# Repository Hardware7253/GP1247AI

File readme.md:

# GP1247AI Driver Board
A GP1247AI clock and animation player, the PCB can also be used as a standalone power supply for the display with external SPI communication through a 10-pin IDC connector.

The [Code](/Code) directory contains the C code for the microcontroller and Python cli tools for syncing the RTC, and writing animations to the device over USB CDC.

## Pictures

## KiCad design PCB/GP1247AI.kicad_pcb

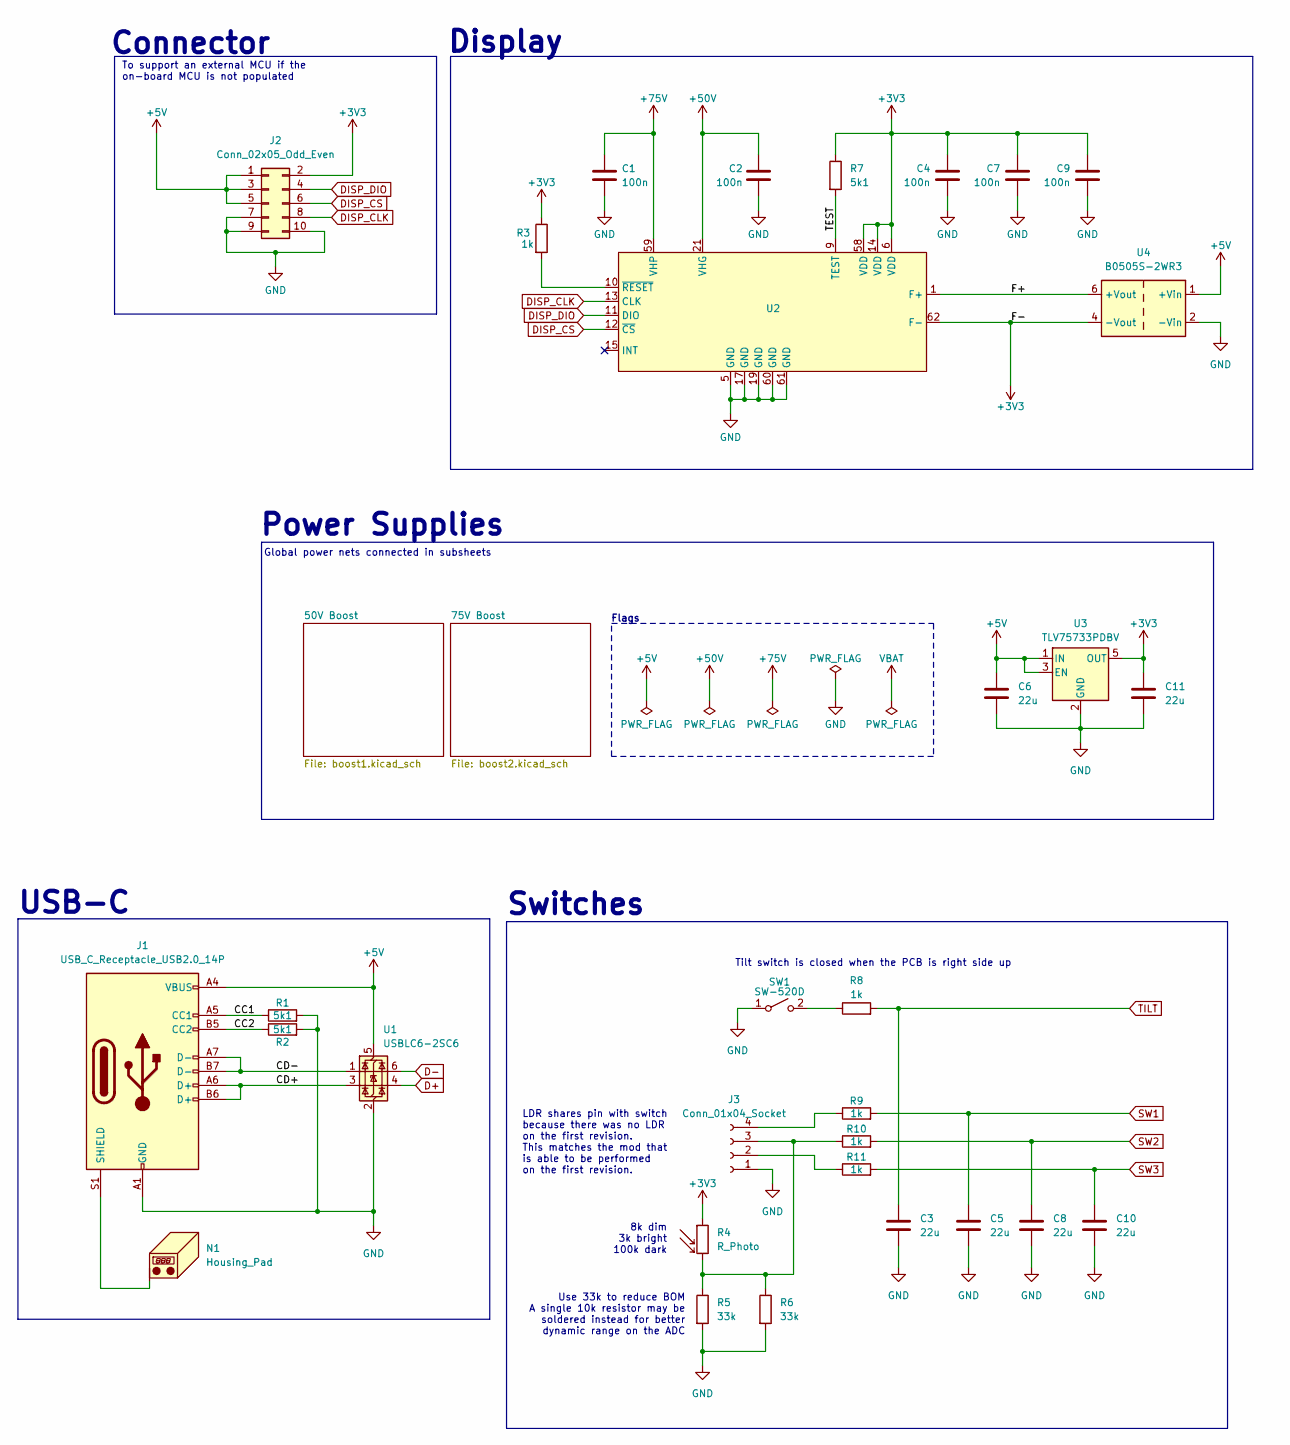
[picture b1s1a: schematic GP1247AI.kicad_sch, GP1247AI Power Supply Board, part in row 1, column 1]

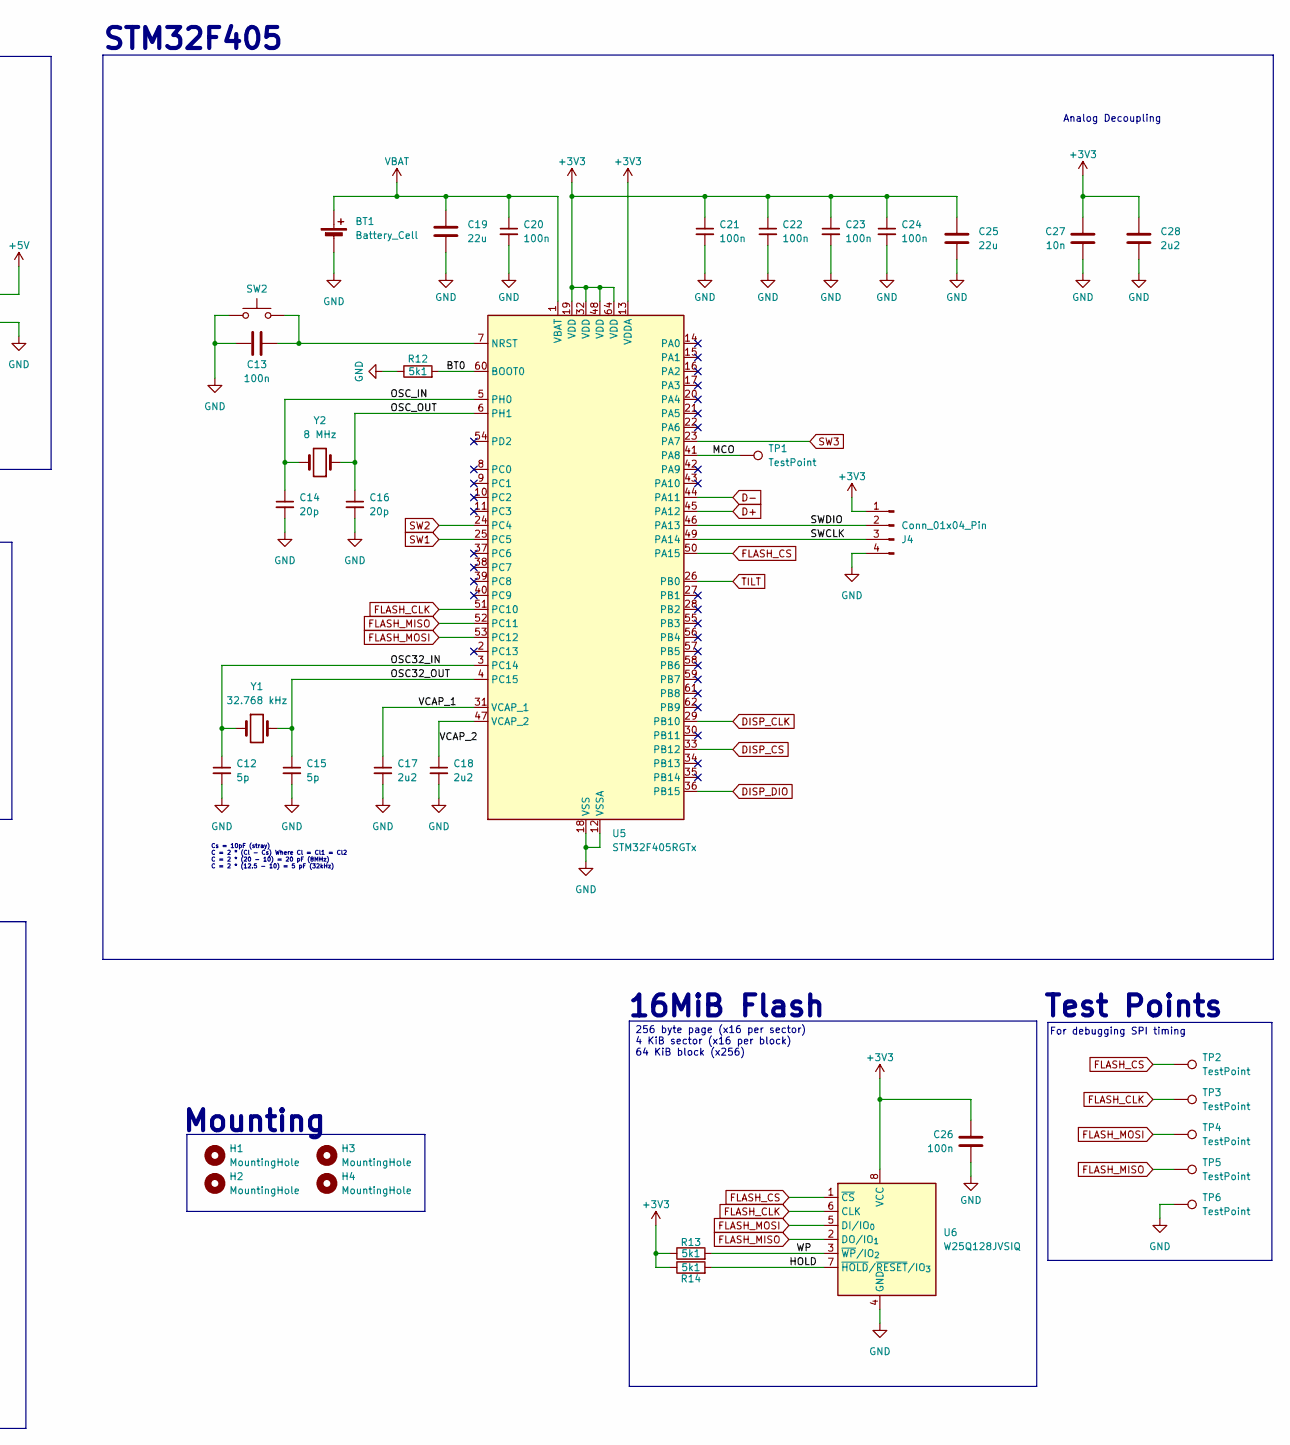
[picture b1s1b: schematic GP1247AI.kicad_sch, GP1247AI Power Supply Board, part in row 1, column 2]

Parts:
BT1: Battery_Cell; QIJEY CR2032-BS-6-1; LCSC PART # C70377
C1, C2, C4, C7, C9, C13, C20, C21, C22, C23, C24, C26: 100n; C_0603_1608Metric; LCSC PART # C15725
C3, C5, C6, C8, C10, C11, C19, C25: 22u; C_0603_1608Metric; LCSC PART # C7432770
C12, C15: 5p; C_0603_1608Metric; LCSC PART # C327203
C14, C16: 20p; C_0603_1608Metric; LCSC PART # C326779
C17, C18, C28: 2u2; C_0603_1608Metric; LCSC PART # C23630
C27: 10n; C_0603_1608Metric; LCSC PART # C15725
H1, H2, H3, H4: MountingHole; MountingHole_3.2mm_M3
J1: USB_C_Receptacle_USB2.0_14P; USB_TYPE-C-31-M-12; LCSC PART # C165948
J2: Conn_02x05_Odd_Even; IDC-Header_2x05_P2.54mm_Vertical
J3: Conn_01x04_Socket; PinSocket_1x04_P2.54mm_Horizontal; LCSC PART # C2897386
J4: Conn_01x04_Pin; PinHeader_1x04_P2.54mm_Vertical
N1: Housing_Pad; TestPoint_Pad_2.0x2.0mm
R1, R2, R7, R12, R13, R14: 5k1; R_0603_1608Metric; LCSC PART # C23186
R3, R8, R9, R10, R11: 1k; R_0603_1608Metric; LCSC PART # C2907002
R4: R_Photo; R_LDR_5.1x4.3mm_P3.4mm_Vertical; LCSC PART # C125626
R5, R6: 33k; R_0603_1608Metric; LCSC PART # C2907028
SW1: SW-520D; LCSC PART # C2905288
SW2: SW_Push; Korean Hroparts Elec K2-1107ST-A4DW-06; LCSC PART # C118141
TP1: TestPoint; TestPoint_Pad_D1.5mm
TP2, TP3, TP4, TP5, TP6: TestPoint; TestPoint_Keystone_5019_Miniature; LCSC PART # C5199800
U1: USBLC6-2SC6; SOT-23-6; LCSC PART # C7519
U2: GP1247AI
U3: TLV75733PDBV; SOT-23-5; LCSC PART # C485517
U4: B0505S-2WR3; LCSC PART # C7465195
U5: STM32F405RGTx; LQFP-64_10x10mm_P0.5mm; LCSC PART # C15742
U6: W25Q128JVSIQ; SOIC-8_5.3x5.3mm_P1.27mm; LCSC PART # C2613930
Y1: 32.768 kHz; SMD3215-2P; LCSC PART # C42438016
Y2: 8 MHz; Crystal_SMD_5032-2Pin_5.0x3.2mm; LCSC PART # C46613796

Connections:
+3V3: C4.1, C7.1, C9.1, C11.1, C21.1, C22.1, C23.1, C24.1, C25.1, C26.1, C27.1, C28.1, J2.2, J4.1, R3.1, R4.1, R7.1, R13.1, R14.1, U2.6 (VDD), U2.14 (VDD), U2.58 (VDD), U2.62 (F-), U2.63 (F-), U2.64 (F-), U2.65 (F-), U3.5 (OUT), U4.4 (-Vout), U5.13 (VDDA), U5.19 (VDD), U5.32 (VDD), U5.48 (VDD), U5.64 (VDD), U6.8 (VCC)
+5V: C6.1, J1.A4 (VBUS), J1.A9 (VBUS), J1.B4 (VBUS), J1.B9 (VBUS), J2.1, J2.3, J2.5, U1.5 (VBUS), U3.1 (IN), U3.3 (EN), U4.1 (+Vin); also elsewhere on the board
+50V: C2.1, U2.21 (VHG); also elsewhere on the board
+75V: C1.1, U2.59 (VHP); also elsewhere on the board
/BT0: R12.2, U5.60 (BOOT0)
/CC1: J1.A5 (CC1), R1.1
/CC2: J1.B5 (CC2), R2.1
/CD+: J1.A6 (D+), J1.B6 (D+), U1.3 (I/O2)
/CD-: J1.A7 (D-), J1.B7 (D-), U1.1 (I/O1)
/F+: U2.1 (F+), U2.2 (F+), U2.3 (F+), U2.4 (F+), U4.6 (+Vout)
/HOLD: R14.2, U6.7 (~HOLD/~RESET/IO_{3})
/MCO: TP1.1 (1_1), U5.41 (PA8)
/OSC32_IN: C12.1, U5.3 (PC14), Y1.1
/OSC32_OUT: C15.1, U5.4 (PC15), Y1.2
/OSC_IN: C14.1, U5.5 (PH0), Y2.2
/OSC_OUT: C16.1, U5.6 (PH1), Y2.1
/SWCLK: J4.3, U5.49 (PA14)
/SWDIO: J4.2, U5.46 (PA13)
/TEST: R7.2, U2.9 (TEST)
/VCAP_1: C17.1, U5.31 (VCAP_1)
/VCAP_2: C18.1, U5.47 (VCAP_2)
/WP: R13.2, U6.3 (~WP/IO_{2})
D+: U1.4 (I/O2), U5.45 (PA12)
D-: U1.6 (I/O1), U5.44 (PA11)
DISP_CLK: J2.8, U2.13 (CLK), U5.29 (PB10)
DISP_CS: J2.6, U2.12 (~CS), U5.33 (PB12)
DISP_DIO: J2.4, U2.11 (DIO), U5.36 (PB15)
FLASH_CLK: TP3.1 (1_1), U5.51 (PC10), U6.6 (CLK)
FLASH_CS: TP2.1 (1_1), U5.50 (PA15), U6.1 (~CS)
FLASH_MISO: TP5.1 (1_1), U5.52 (PC11), U6.2 (DO/IO_{1})
FLASH_MOSI: TP4.1 (1_1), U5.53 (PC12), U6.5 (DI/IO_{0})
GND: BT1.2 (-), C1.2, C2.2, C3.2, C4.2, C5.2, C6.2, C7.2, C8.2, C9.2, C10.2, C11.2, C12.2, C13.1, C14.2, C15.2, C16.2, C17.2, C18.2, C19.2, C20.2, C21.2, C22.2, C23.2, C24.2, C25.2, C26.2, C27.2, C28.2, J1.A1 (GND), J1.A12 (GND), J1.B1 (GND), J1.B12 (GND), J2.7, J2.9, J2.10, J3.1, J4.4, R1.2, R2.2, R5.2, R6.2, R12.1, SW1.1 (A), SW2.1, TP6.1 (1_1), U1.2 (GND), U2.5 (GND), U2.17 (GND), U2.19 (GND), U2.60 (GND), U2.61 (GND), U3.2 (GND), U4.2 (-Vin), U5.12 (VSSA), U5.18 (VSS), U5.63 (VSS), U6.4 (GND); also elsewhere on the board
unnamed: J1.S1 (SHIELD), N1.1 (PAD_1)
unnamed: J3.2, R11.1
unnamed: J3.3, R4.2, R5.1, R6.1, R10.1
unnamed: J3.4, R9.1
unnamed: R8.1, SW1.2 (B)
unnamed: R3.2, U2.10 (~RESET)
unnamed: C13.2, SW2.2, U5.7 (NRST)
SW1: C5.1, R9.2, U5.25 (PC5)
SW2: C8.1, R10.2, U5.24 (PC4)
SW3: C10.1, R11.2, U5.23 (PA7)
TILT: C3.1, R8.2, U5.26 (PB0)
VBAT: BT1.1 (+), C19.1, C20.1, U5.1 (VBAT)

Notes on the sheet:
Cs = 10pF (stray) C = 2 * (Cl - Cs) Where Cl = Cl1 = Cl2 C = 2 * (20 - 10) = 20 pF (8MHz) C = 2 * (12.5 - 10) = 5 pF (32kHz)
Mounting
LDR shares pin with switch because there was no LDR on the first revision. This matches the mod that is able to be performed on the first revision.
Display
Tilt switch is closed when the PCB is right side up
USB-C
For debugging SPI timing
8k dim 3k bright 100k dark
256 byte page (x16 per sector) 4 KiB sector (x16 per block) 64 KiB block (x256)
Switches
Global power nets connected in subsheets
To support an external MCU if the on-board MCU is not populated
Power Supplies
STM32F405
Connector
Use 33k to reduce BOM A single 10k resistor may be soldered instead for better dynamic range on the ADC
Flags
Test Points
16MiB Flash
Analog Decoupling

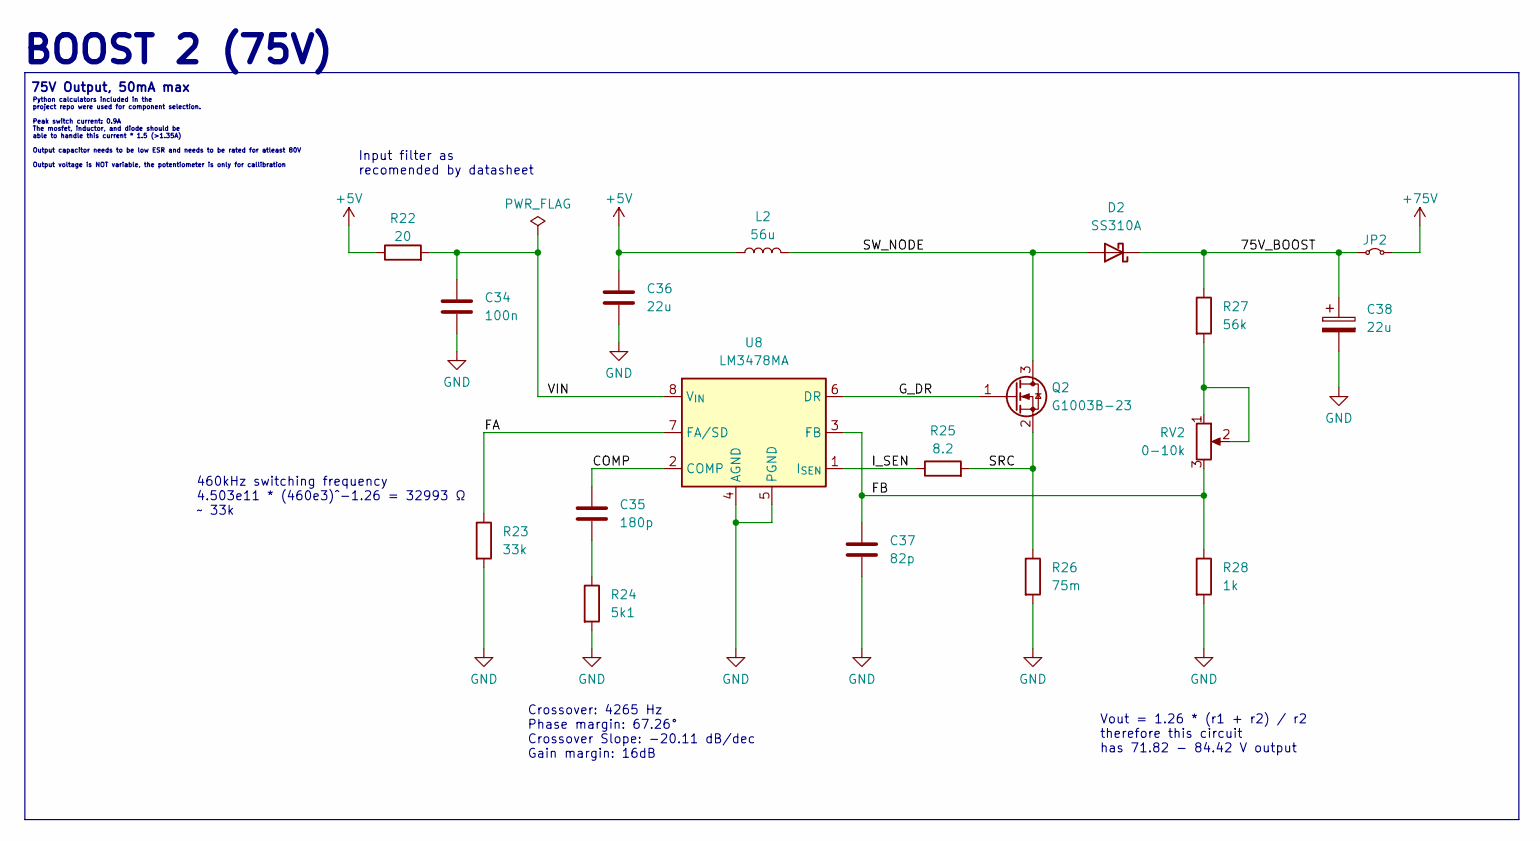
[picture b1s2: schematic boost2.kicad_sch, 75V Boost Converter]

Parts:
C34: 100n; C_0603_1608Metric; LCSC PART # C15725
C35: 180p; C_0603_1608Metric; LCSC PART # C2170987
C36: 22u; C_0603_1608Metric; LCSC PART # C7432770
C37: 82p; C_0603_1608Metric; LCSC PART # C1864236
C38: 22u; CP_Radial_D6.3mm_P2.50mm; LCSC PART # C44606504
D2: SS310A; D_SMA; LCSC PART # C48996628
JP2: Jumper_2_Small_Bridged; PinHeader_1x02_P2.54mm_Vertical
L2: 56u; Chilisin SCDS105R; LCSC PART # C329728
Q2: G1003B-23; SOT-23-3; LCSC PART # C22362809
R22: 20; R_0603_1608Metric; LCSC PART # C2907012
R23: 33k; R_0603_1608Metric; LCSC PART # C2907028
R24: 5k1; R_0603_1608Metric; LCSC PART # C23186
R25: 8.2; R_0603_1608Metric; LCSC PART # C861594
R26: 75m; R_1206_3216Metric; LCSC PART # C2904225
R27: 56k; R_0603_1608Metric; LCSC PART # C2907053
R28: 1k; R_0603_1608Metric; LCSC PART # C2907002
RV2: 0-10k; Potentiometer_Bourns_TC33X_Vertical; LCSC PART # C719176
U8: LM3478MA; SOIC-8_3.9x4.9mm_P1.27mm; LCSC PART # C115907

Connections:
+5V: C36.1, L2.1, R22.1; also elsewhere on the board
+75V: JP2.2 (B); also elsewhere on the board
/75V Boost/75V_BOOST: C38.1, D2.1 (K), JP2.1 (A), R27.1
/75V Boost/COMP: C35.1, U8.2 (COMP)
/75V Boost/FA: R23.1, U8.7 (FA/SD)
/75V Boost/FB: C37.1, R28.1, RV2.3, U8.3 (FB)
/75V Boost/G_DR: Q2.1 (G), U8.6 (DR)
/75V Boost/I_SEN: R25.1, U8.1 (I_{SEN})
/75V Boost/SRC: Q2.2 (S), R25.2, R26.1
/75V Boost/SW_NODE: D2.2 (A), L2.2, Q2.3 (D)
/75V Boost/VIN: C34.1, R22.2, U8.8 (V_{IN})
GND: C34.2, C36.2, C37.2, C38.2, R23.2, R24.2, R26.2, R28.2, U8.4 (AGND), U8.5 (PGND); also elsewhere on the board
unnamed: C35.2, R24.1
unnamed: R27.2, RV2.1, RV2.2

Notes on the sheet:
75V Output, 50mA max
460kHz switching frequency 4.503e11 * (460e3)^-1.26 = 32993 Ω ~ 33k
BOOST 2 (75V)
Python calculators included in the project repo were used for component selection. Peak switch current: 0.9A The mosfet, inductor, and diode should be able to handle this current * 1.5 (>1.35A) Output capacitor needs to be low ESR and needs to be rated for atleast 80V Output voltage is NOT variable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
Input filter as recomended by datasheet
Vout = 1.26 * (r1 + r2) / r2 therefore this circuit has 71.82 - 84.42 V output
Crossover: 4265 Hz Phase margin: 67.26° Crossover Slope: -20.11 dB/dec Gain margin: 16dB

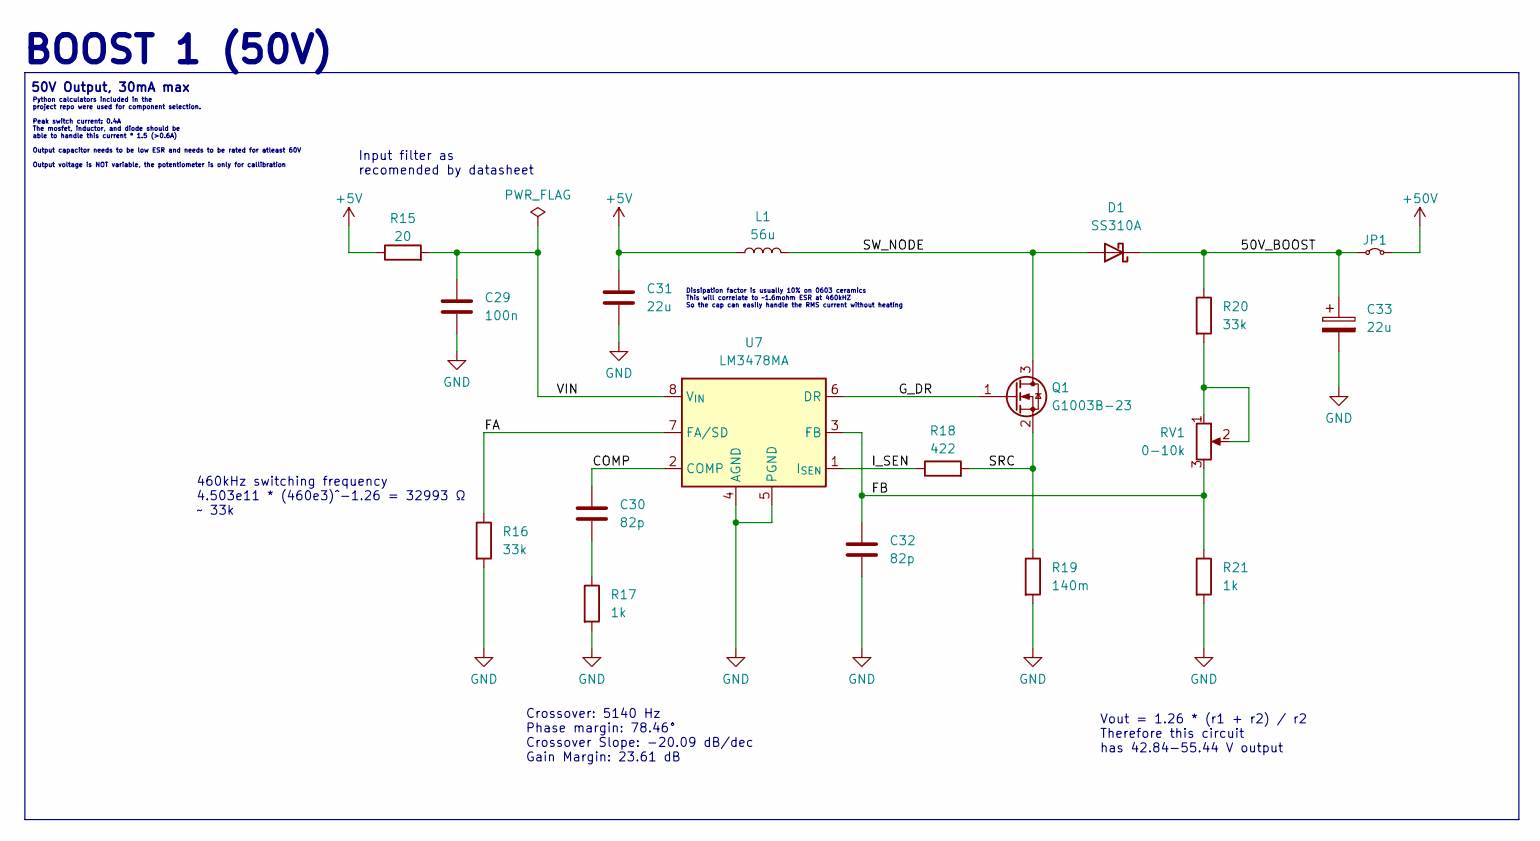
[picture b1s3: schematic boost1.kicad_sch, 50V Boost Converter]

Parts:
C29: 100n; C_0603_1608Metric; LCSC PART # C15725
C30, C32: 82p; C_0603_1608Metric; LCSC PART # C1864236
C31: 22u; C_0603_1608Metric; LCSC PART # C7432770
C33: 22u; CP_Radial_D6.3mm_P2.50mm; LCSC PART # C44606504
D1: SS310A; D_SMA; LCSC PART # C48996628
JP1: Jumper_2_Small_Bridged; PinHeader_1x02_P2.54mm_Vertical
L1: 56u; Chilisin SCDS105R; LCSC PART # C329728
Q1: G1003B-23; SOT-23-3; LCSC PART # C22362809
R15: 20; R_0603_1608Metric; LCSC PART # C2907012
R16, R20: 33k; R_0603_1608Metric; LCSC PART # C2907028
R17, R21: 1k; R_0603_1608Metric; LCSC PART # C2907002
R18: 422; R_0603_1608Metric; LCSC PART # C5204003
R19: 140m; R_1206_3216Metric; LCSC PART # C37935
RV1: 0-10k; Potentiometer_Bourns_TC33X_Vertical; LCSC PART # C719176
U7: LM3478MA; SOIC-8_3.9x4.9mm_P1.27mm; LCSC PART # C115907

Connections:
+5V: C31.1, L1.1, R15.1; also elsewhere on the board
+50V: JP1.2 (B); also elsewhere on the board
/50V Boost/50V_BOOST: C33.1, D1.1 (K), JP1.1 (A), R20.1
/50V Boost/COMP: C30.1, U7.2 (COMP)
/50V Boost/FA: R16.1, U7.7 (FA/SD)
/50V Boost/FB: C32.1, R21.1, RV1.3, U7.3 (FB)
/50V Boost/G_DR: Q1.1 (G), U7.6 (DR)
/50V Boost/I_SEN: R18.1, U7.1 (I_{SEN})
/50V Boost/SRC: Q1.2 (S), R18.2, R19.1
/50V Boost/SW_NODE: D1.2 (A), L1.2, Q1.3 (D)
/50V Boost/VIN: C29.1, R15.2, U7.8 (V_{IN})
GND: C29.2, C31.2, C32.2, C33.2, R16.2, R17.2, R19.2, R21.2, U7.4 (AGND), U7.5 (PGND); also elsewhere on the board
unnamed: C30.2, R17.1
unnamed: R20.2, RV1.1, RV1.2

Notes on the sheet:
BOOST 1 (50V)
50V Output, 30mA max
Crossover: 5140 Hz Phase margin: 78.46° Crossover Slope: -20.09 dB/dec Gain Margin: 23.61 dB
Input filter as recomended by datasheet
Vout = 1.26 * (r1 + r2) / r2 Therefore this circuit has 42.84-55.44 V output
460kHz switching frequency 4.503e11 * (460e3)^-1.26 = 32993 Ω ~ 33k
Python calculators included in the project repo were used for component selection. Peak switch current: 0.4A The mosfet, inductor, and diode should be able to handle this current * 1.5 (>0.6A) Output capacitor needs to be low ESR and needs to be rated for atleast 60V Output voltage is NOT variable,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
Dissipation factor is usually 10% on 0603 ceramics This will correlate to ~1.6mohm ESR at 460kHZ So the cap can easily handle the RMS current without heating

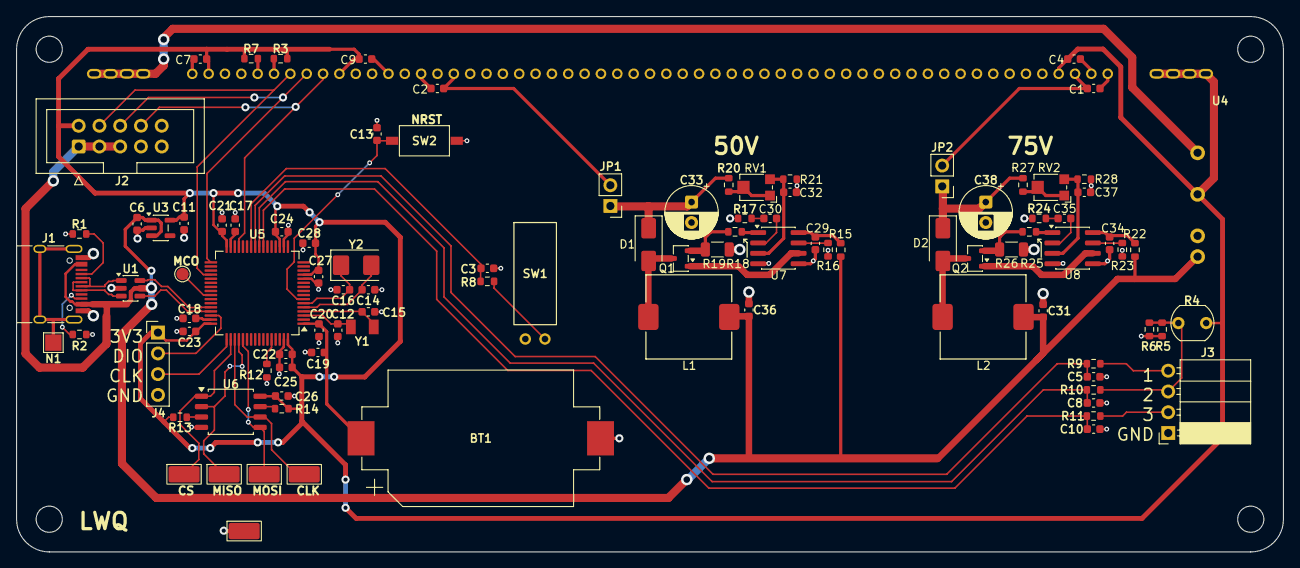
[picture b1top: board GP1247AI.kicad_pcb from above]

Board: 2 copper layers, 155.0 x 65.5 mm, 104 parts (1 on the bottom side), 66 nets.

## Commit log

2026-02-09 Added onboard MCU
2026-02-13 Added LDR to PCB
    Forgot the LDR in the first revision. It was added to the PCB in such a
    way to be pin compatible with an LDR mod on the first revision.
    Also re-organised project into PCB, CAD, and Code directories
2026-02-19 Updated manufacturing outputs for case files
2026-02-26 Added code
    Code directory now contains embedded c code for the onboard
    microcontroller, and PC side python CLI programs for uploading
    animations and setting RTC time on the device.
    This is one commit but the code has been in progress for 1.5 months.
2026-03-06 Add 12 hour mode and night mode
    Night mode sets the display brightness low enough to not illuminate a
    pitch black room
2026-03-14 Added old streaming code
    This actually predates every commit on main by a month or so.
    Initially the plan was to stream from the PC instead of play animations
    from flash.
2026-03-19 Update submodules and readme
2026-03-19 Add images to readm
2026-05-15 Fixed floating boot0
2026-05-15 Updated manufacturing outputs
2026-05-16 Remove old BOM
2026-06-12 Add MIT License to the project
2026-06-22 Fixed swapped reference designators
    Fixed swapped reference designators on the silkscreen for: R15 & R16, R22 & R23, and C14 & C15
